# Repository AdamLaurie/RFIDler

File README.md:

# RFIDler

## Firmware

The 'firmware' directory contains code for the dev platform(s).
Currently that is Pic32, but we will add a new section if and when required.

## Hardware

A fully built RFIDler board can be purchased here: [http://rfidiot.org/#Hardware](http://rfidiot.org/#Hardware)

### Pic32

The main microcontroller is a [Microchip PIC32MX795F512L](http://www.microchip.com/wwwproducts/Devices.aspx?dDocName=en545660)

## Software Build environment

The project was developed in Mplab-X IDE V3.20 under Linux, but can also be built under Windows & Mac:

* [Linux] (http://www.microchip.com/mplabx-ide-linux-installer)

* [Windows] (http://www.microchip.com/mplabx-ide-windows-installer)

* [Mac] (http://www.microchip.com/mplabx-ide-osx-installer)

The compiler used was the free version of Microchip's XC32 V1.40:

* [Linux] (http://www.microchip.com/mplabxc32linux)

* [Windows] (http://www.microchip.com/mplabxc32windows)

* [Mac] (http://www.microchip.com/mplabxc32osx)

USB stack and peripheral support is provided by [Microchip Application Library v2013-06-15] (http://www.microchip.com/pagehandler/en-us/devtools/mla/archives.html):

* [Linux](http://ww1.microchip.com/downloads/en/softwarelibrary/microchip-libraries-for-applications-v2013-06-15-linux-installer.run)
  - Install to /opt/microchip/microchip_solutions_v2013-06-15/
  - Note: if the installer fails to start, try adding the run-time option '--mode text'
* [Windows](http://ww1.microchip.com/downloads/en/softwarelibrary/microchip-libraries-for-applications-v2013-06-15-windows-installer.exe)
  - Install to installer default location
* [Mac](http://ww1.microchip.com/downloads/en/softwarelibrary/microchip-libraries-for-applications-v2013-06-15-osx-installer.dmg)
  - Install to installer default location

and [PIC32 Peripheral Library] (http://www.microchip.com/SWLibraryWeb/product.aspx?product=PIC32%20Peripheral%20Library):

* [Linux](http://ww1.microchip.com/downloads/en/DeviceDoc/PIC32%20Legacy%20Peripheral%20Libraries%20Linux.tar)
  - Install to /opt/microchip/xc32/v1.40
* [Windows](http://ww1.microchip.com/downloads/en/DeviceDoc/PIC32%20Legacy%20Peripheral%20Libraries.zip)
  - Install to installer default location
* [Mac](http://ww1.microchip.com/downloads/en/DeviceDoc/PIC32%20Legacy%20Peripheral%20Libraries%20MACOS.zip)
  - Install to installer default location

### Bootloader

When the Bootloader is running the RFIDler appears on the USB as a HID, and waits for new RFIDler firmware to install in Flash memory.
There are several ways of entering the Bootloader, see "Loading new Firmware" section below.

USB HID Bootloader is provided by the [UBW32 project](http://www.schmalzhaus.com/UBW32/FW/HIDBoot.X/HIDBoot.X.zip)

For convenience, a copy of the bootloader hex and an MPLAB hex load project is provided in `firmware/Pic32/HIDBoot_MX795_Hex_Load.X`

The Bootloader client, mphidflash, runs on Linux/Mac/Windows and transmits & verifies the new firmware.

https://github.com/AdamLaurie/mphidflash

#### Notes

mphidflash v1.3 has some known bugs where for some ROM binaries programming fails and a verification error is reported.
	
If you hit this problem check for a newer release of mphidflash. Pre-compiled executables for all platforms are available [here](https://github.com/AdamLaurie/mphidflash)

### Software Build

Install packages as above.

Clone this repo to your local hard disk.

1. Start MPLAB X IDE
2. Choose `File/Open Project/`
3. Browse to RFIDler.X and click 'Open Project'

#### Windows

If you are running Windows, you will need to change the default Linux library to the local Windows version:

UPDATE NEEDED TO THIS SECTION!

(There are bugs in MPLAB X and GNU make such that paths to libraries containing spaces are not always processed correctly, 
and the default install path on Windows contains spaces so making the copy is the simplest solution.)

#### Mac OS X

If you are running Mac OS X, you will need to change the default Linux library to the local Mac version:

UPDATE NEEDED TO THIS SECTION!

### Connections

The device can be powered via the USB port, and, if connected to a PC, will provide a
management CLI/API via USB-Serial CDC at 115200 baud (8 bit, No Parity, 1 Stop Bit, No Handshaking/Flow Control).

The CLI/API is also accessible via 3.3v or 5v UART on pins RG7 (UART3 RX) and RG8 (UART3 TX), also at 115200 baud.

When you connect with USB for the first time, you may need to perform some configuration steps:

#### Linux

Create a rule file for UDEV to allow non-root access to the file, and also disable modem manager access. An appropriate file can be found in the MPLAB project
under the "Linux Support" tab. Copy this file to `/etc/udev/rules.d` and run `sudo udevadm control --reload-rules`

This file can also be found in this repo at: linux-support/71-rfidler-lf-cdc-blacklist.rules

#### Windows

Windows drivers can be found in the 'Windows Driver' tab of the MPLAB project

To connect, any serial terminal emulator should work, but we recommend:

* Linux: minicom (`sudo apt-get install minicom`)
* Windows: [PuTTY](http://www.chiark.greenend.org.uk/~sgtatham/putty/)
* Mac OS X: minicom (install: [brew](https://brew.sh/) minicom) or SerialTools (free from the App Store)

Example linux connection:

	minicom -D /dev/ttyACM1 -b 115200 

Once connected, hit `<ENTER>` to see the HELP screen and switch to CLI mode, or send commands to remain in API mode.

In API mode, all commands are as per CLI mode, and will be ACK'd by a single '.' or NACK'd by '!' if command fails
or '?' if it is not recognised. Other output is command dependant.

## Loading new Firmware

Enter bootloader mode 

* either from the menu (`BL`)
* _or_ by holding down button `BOOTLOADER` while simultaneously 
	* plugging in the USB cable 
	* _or_ pressing the 'RESET' button.

LED6 and LED5 will show stable orange light to confirm bootloader mode has been entered.

	#~/tools/mphidflash-1.6/binaries/mphidflash-1.6-linux-64 -r -w firmware/Pic32/RFIDler.X/dist/debug/production/RFIDler.X.production.hex 
	USB HID device found: 503808 bytes free
	Device family: PIC32

	Erasing...
	Writing hex file 'RFIDler.X.production.hex':......[...removed for brevity...]
	Verifying:.... [...removed for brevity...]
	Resetting device...

You can verify the flashing via `version`

	*RFIDler> version
	0071-beta

### Linux:

`dmesg` should show the following:

	generic-usb 0003:04D8:003C.0003: hiddev0,hidraw1: USB HID v1.11 Device [Microchip Technology Inc. USB HID Bootloader] on usb-0000:00:1d.0-1.1.2.1/input0

To flash the code, `cd` to the top of the repo and run:

		mphidflash -r -w firmware/Pic32/RFIDler.X/dist/default/production/RFIDler.X.production.hex

The device will be programmed and will then reboot. `dmesg` should show:

	usb 2-1.1.2.1: USB disconnect, device number 19
	usb 2-1.1.2.1: new full speed USB device number 20 using ehci_hcd
	cdc_acm 2-1.1.2.1:1.0: This device cannot do calls on its own. It is not a modem.
	cdc_acm 2-1.1.2.1:1.0: ttyACM3: USB ACM device

### Windows

???

### Mac OS X

## Install mphidflash from source
Option 1, v1.6:
```shell
curl https://github.com/AdamLaurie/mphidflash/blob/master/dist/mphidflash-1.6-src.tar.gz > mphidflash1-6.tar.gz
mkdir mphidflash1-6
tar -zxvf mphidflash1-6.tar.gz -C mphidflash1-6
cd mphidflash1-6
mkdir binaries
sudo make install64
```

Option 2, latest:
```shell
git clone https://github.com/AdamLaurie/mphidflash.git
cd mphidflash
sudo make install64
```

## Flash device
```shell
cd #RFIDler repo
mphidflash -r -w firmware/Pic32/RFIDler.X/dist/debug/production/RFIDler.X.production.hex
```

## See Also

(python shell command line interfacee)[python/README.md]

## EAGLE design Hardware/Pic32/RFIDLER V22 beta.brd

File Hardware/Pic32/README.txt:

Rfidler Beta V22 By Zac Franken For Aperture Labs Ltd

These files are licenced under the creative commons licence See the seperate COPYING file

Some of the analog portion of RFIDler comes from a design by edude: http://playground.arduino.cc/Main/DIYRFIDReader#.Uz8tg1cmBaT
which is based on a schematic by Micah Dowty: http://scanlime.org/2008/08/simplest-rfid-reader

Rfidler Hardware Features:

Detection and decoding of ASK, FSK, and PSK RFID Low frequency tags ~125KHz

Emulation of ASK, FSK, and PSK RFID Low frequency tags

Sniffing of ASK, FSK, and PSK RFID Low frequency tags

Adjustment of comparator thresholds via a digital pot via software, a trim pot and a fixed value resistor voltage divider.

SD card interface

Integrated Chip Card interface

Relay driver

USB interface

Serial interface

Wiegand interfaces

User LED

User button

and an as yet untested LC (Inductance and Capacitance) meter circuit (Still in development) for testing the inductance of your own coils.

There is more to come here, but I wanted to get the schematics up as soon as I could.

Zac

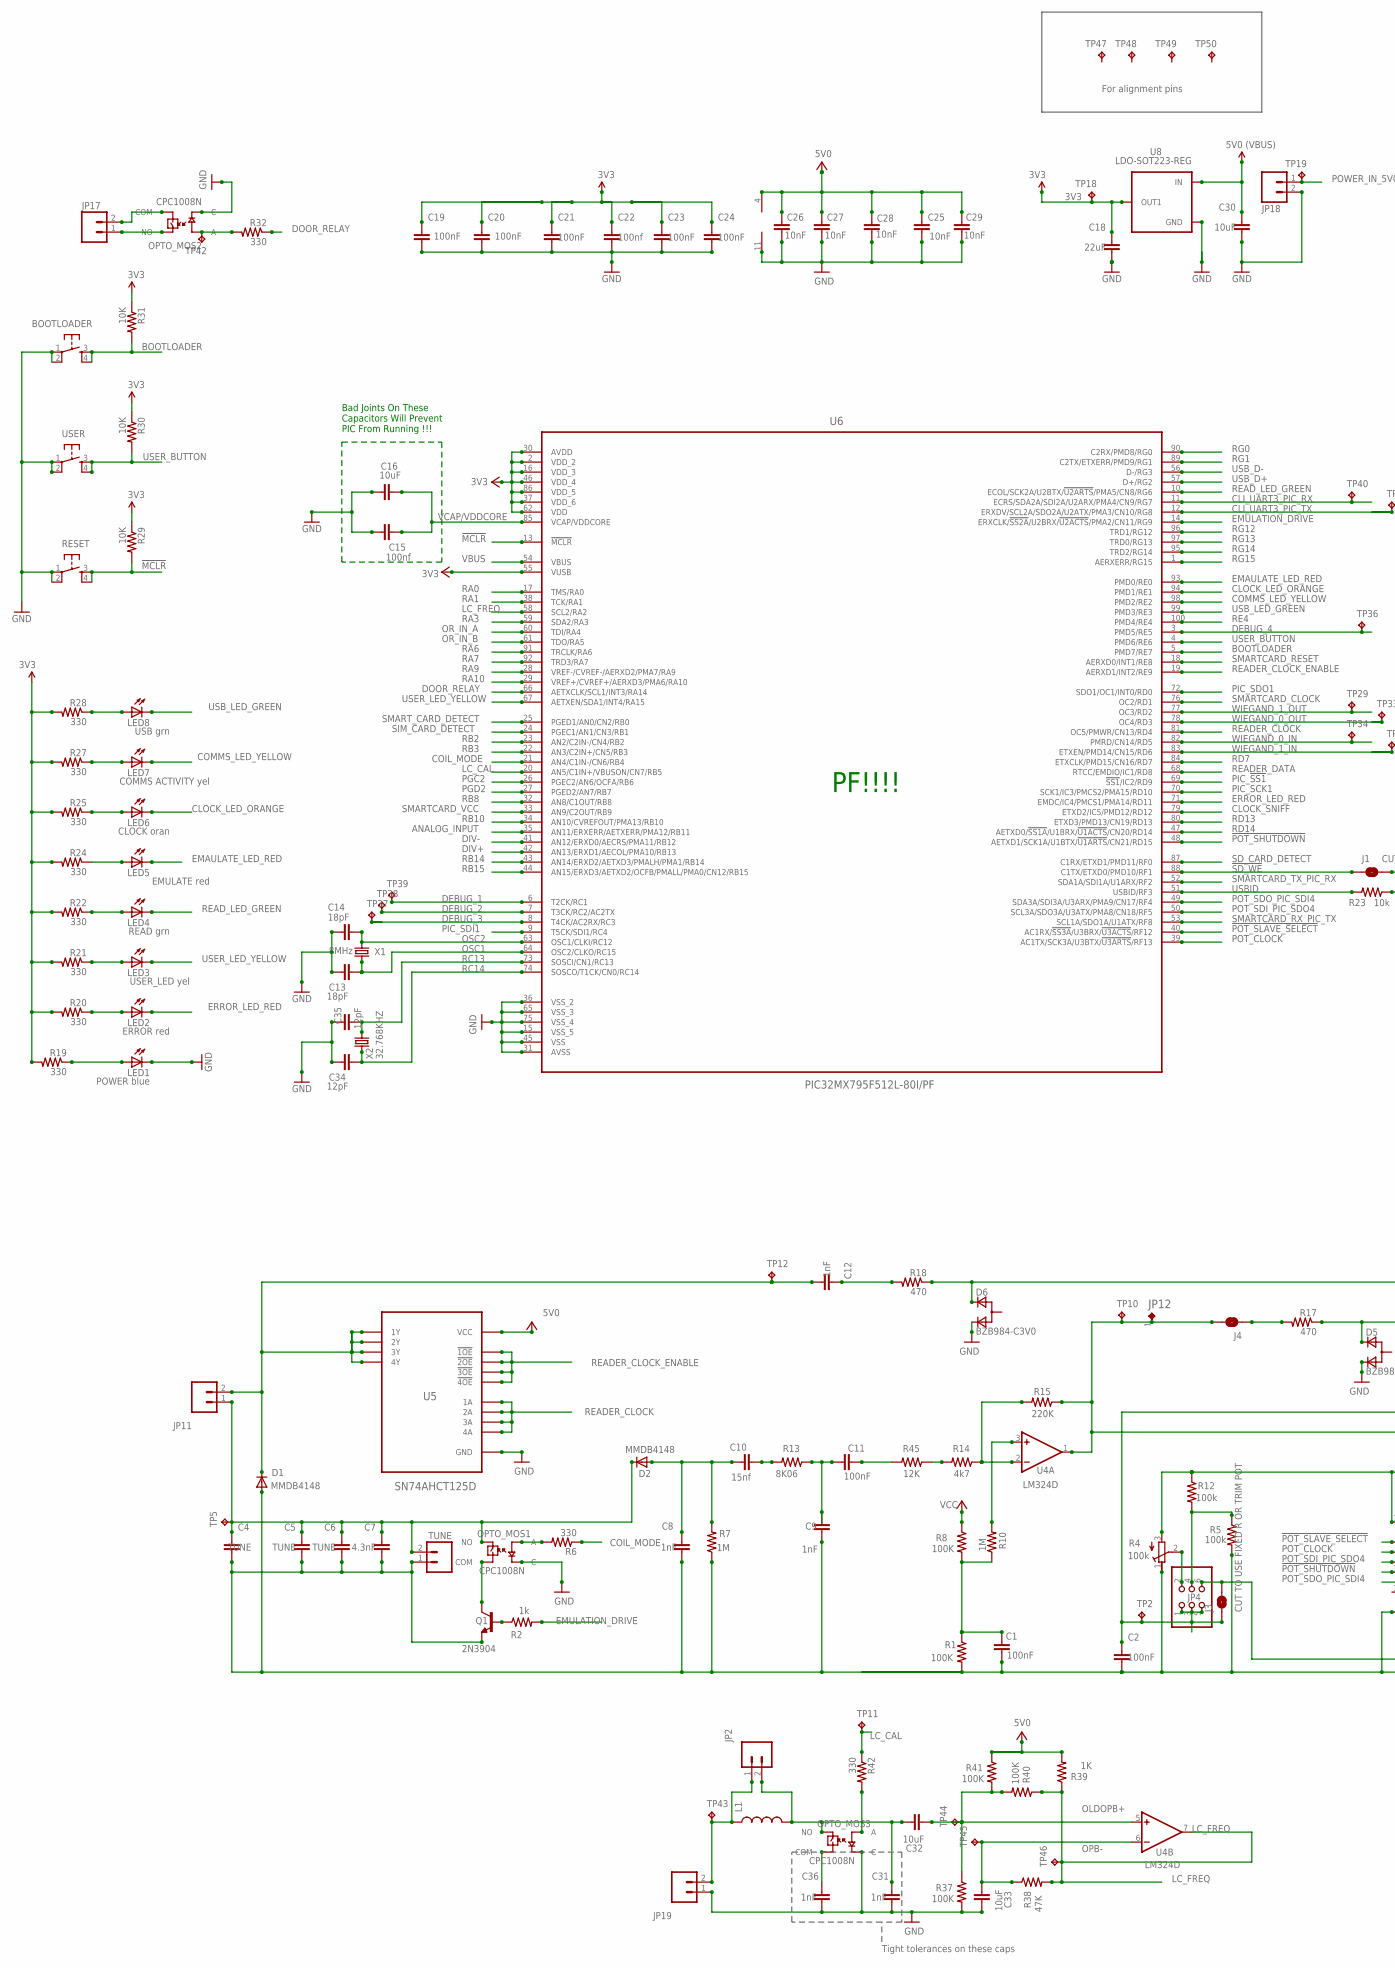
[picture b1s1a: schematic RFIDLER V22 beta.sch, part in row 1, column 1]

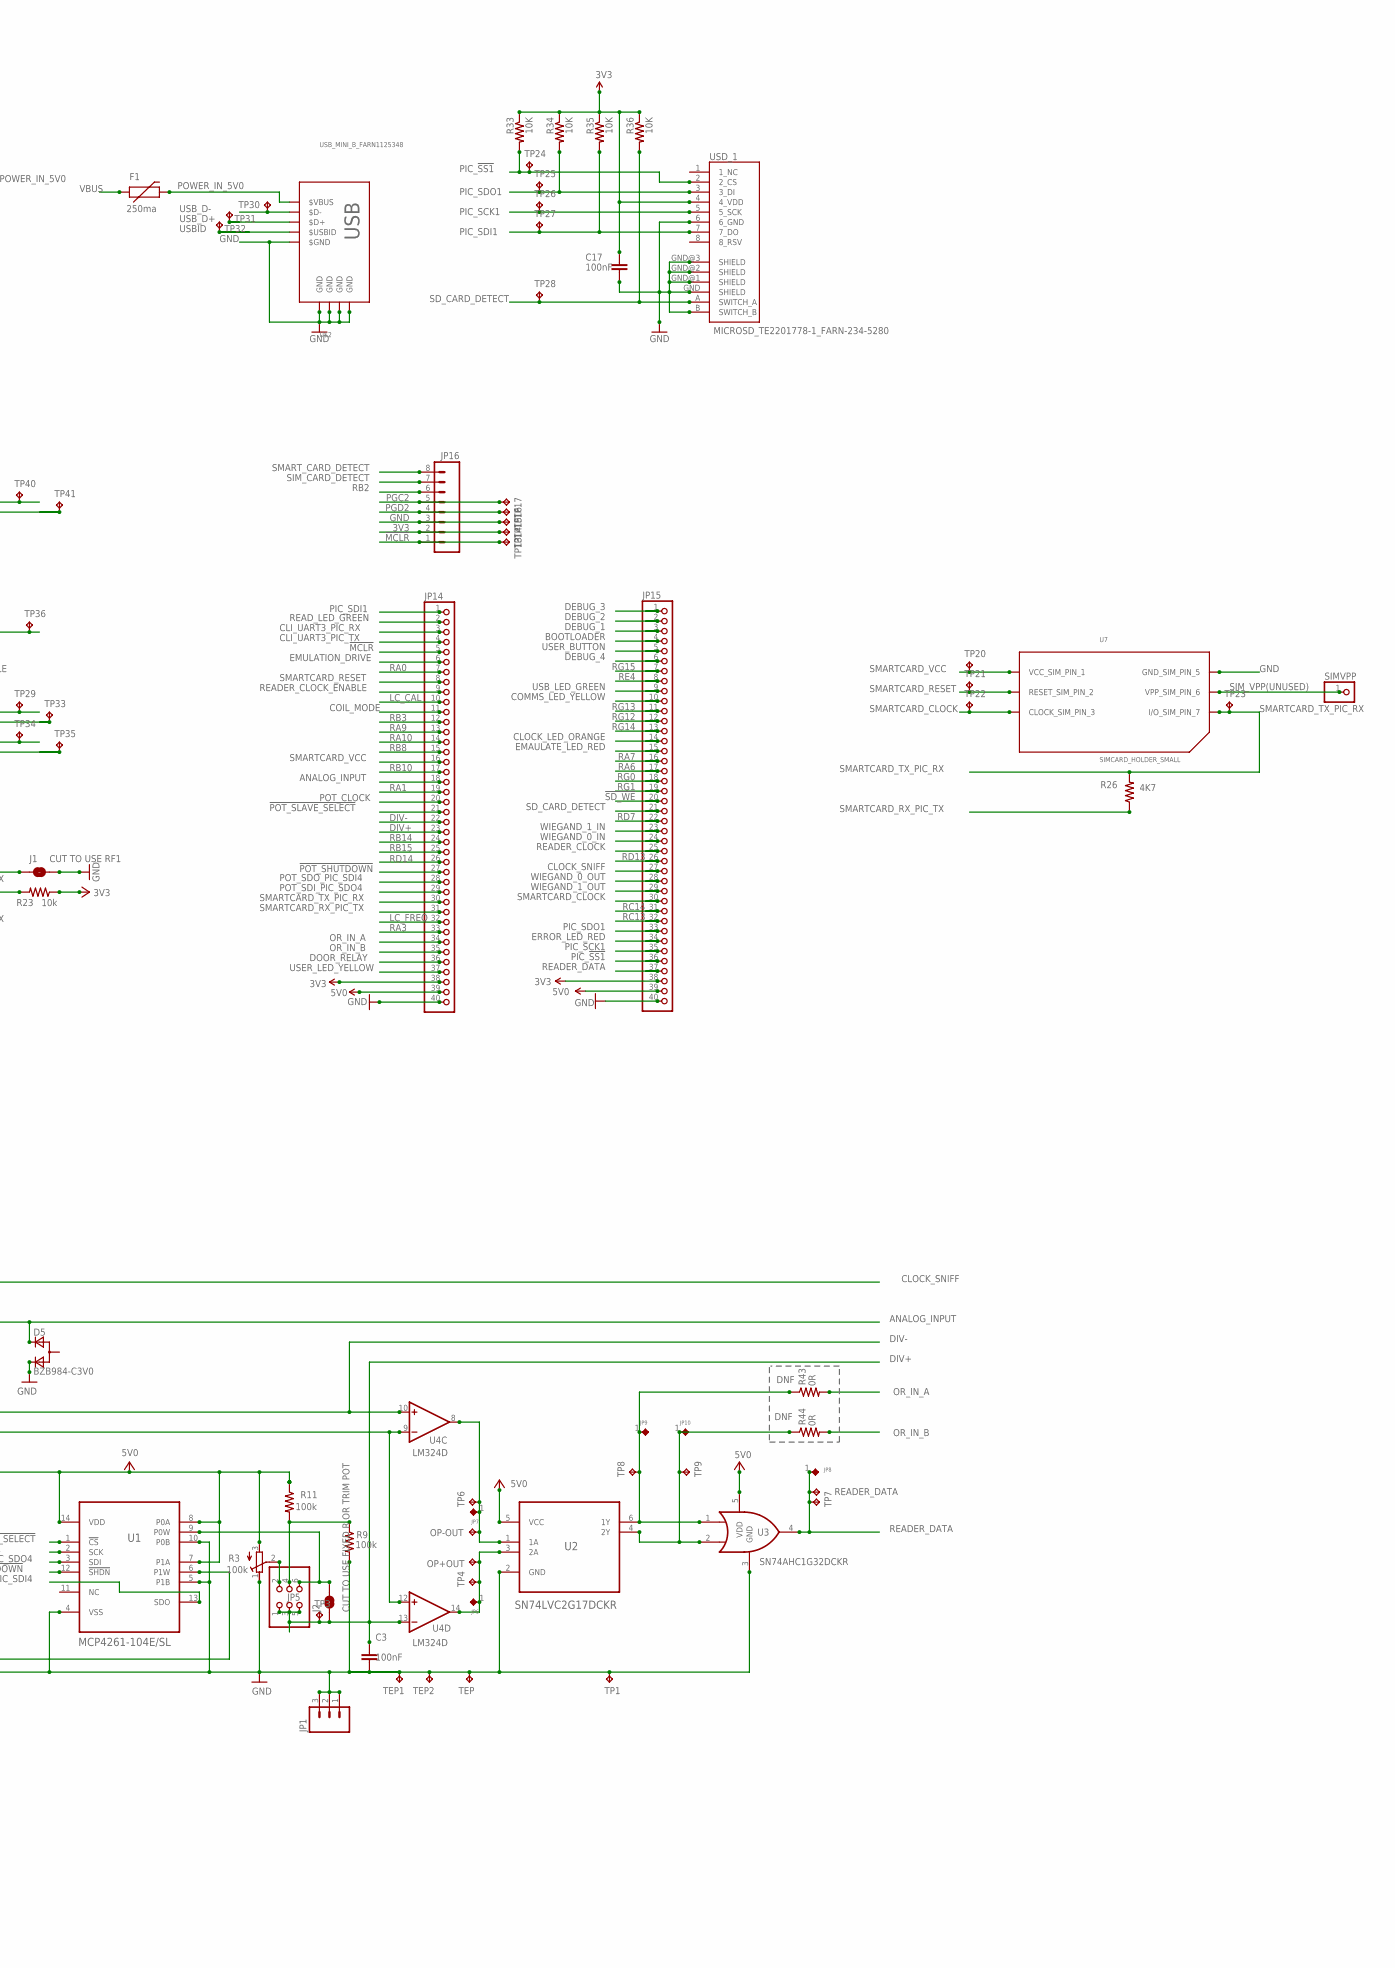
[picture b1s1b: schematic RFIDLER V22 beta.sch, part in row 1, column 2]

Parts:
BOOTLOADER: TAC_SWITCHSMD; TACTILE_SWITCH_SMD; TOLERANCE ?; FARNELL 9471880
C1: 100nF; 0603-CAP; TOLERANCE ?; PARTNO currently rs 264-4646; FARNELL 2332586
C2: 100nF; C0603; TOLERANCE ?; PARTNO currently rs 264-4646; FARNELL 2332586
C3: 100nF; C0603; TOLERANCE ?; PARTNO ?; FARNELL 2332586
C4, C5, C6: TUNE; C0603; TOLERANCE ?; PARTNO ?; FARNELL DNF
C7: 4.3nF; C0603; TOLERANCE 1%; PARTNO ?; FARNELL 1865494
C8, C9, C12: 1nF; C0603; TOLERANCE ?; PARTNO ?; FARNELL 1414606
C10: 15nf; C0603; TOLERANCE ?; PARTNO ?; FARNELL 2070401
C11: 100nF; C0603; TOLERANCE ?; PARTNO currently rs2644646; FARNELL 2332586
C13, C14: 18pF; C0603; TOLERANCE ?; FARNELL 1612182
C15: 100nf; C0603; TOLERANCE Cuurently rs 264 4646; FARNELL 2332586
C16, C30: 10uF; C0805; TOLERANCE ?; FARNELL 1867958
C17: 100nF; C0603; TOLERANCE Crrently rs 264 4646; FARNELL DNF
C18: 22uF; C0805; TOLERANCE ?; FARNELL 1867956
C19, C20, C21, C23, C24: 100nF; C0603; TOLERANCE Crrently rs 264 4646; FARNELL 2332586
C22: 100nf; C0603; TOLERANCE Crrently rs 264 4646; FARNELL 2332586
C25, C26, C27, C28, C29: 10nF; C0603; TOLERANCE ?; PARTNO ?; FARNELL 1301715
C31, C36: 1nF; C0603; TOLERANCE ?; PARTNO ?; FARNELL DNF
C32, C33: 10uF; C0805; TOLERANCE ?; FARNELL DNF
C34, C35: 12pF; C0603; TOLERANCE ?; FARNELL DNF
D1, D2: MMDB4148; SOT23-3; TOLERANCE ?; PARTNO ?; FARNELL 2069338
D5, D6: BZB984-C3V0; SOT663; FARNELL 8735310
F1: 250ma; PTC-1206; FARNELL 1596990
J1: CUT TO USE RF1; SJ_2S-TRACE
J2, J3: CUT TO USE FIXED R OR TRIM POT; SJ_2S-TRACE
J4: SOLDERJUMPERTRACE; SJ_2S-TRACE
JP1: M03LOCK_LONGPADS; 1X03_LOCK_LONGPADS; FARNELL DNF
JP2, JP18, JP19: M02LOCK_LONGPADS; 1X02_LOCK_LONGPADS; TOLERANCE ?; PARTNO ?; FARNELL DNF
JP4, JP5: PINHD-2X3; 2X03; TOLERANCE ?; PARTNO ?; FARNELL DNF
JP6, JP7, JP8, JP9, JP10, JP12: PINHD-1X1; 1X01; TOLERANCE ?; FARNELL DNF
JP11: M02LOCK_LONGPADS; 1X02_LOCK_LONGPADS; TOLERANCE ?; PARTNO ?; FARNELL 1550562 standard 2 PIN HEADER
JP14, JP15: PINHD-1X40; 1X40; FARNELL DNF
JP16: M08; 1X08; TOLERANCE ?; FARNELL DNF
JP17: M02LOCK_LONGPADS; 1X02_LOCK_LONGPADS; FARNELL DNF
L1: INDUCTOR0603; 0603; FARNELL DNF
LED1: POWER blue; LED-0603; TOLERANCE ?; FARNELL 2217972
LED2: ERROR red; LED-0603; TOLERANCE ?; FARNELL 2099221
LED3: USER_LED yel; LED-0603; TOLERANCE ?; FARNELL 2146436
LED4: READ grn; LED-0603; TOLERANCE ?; FARNELL 2146434
LED5: EMULATE red; LED-0603; TOLERANCE ?; FARNELL 2099221
LED6: CLOCK oran; LED-0603; TOLERANCE ?; FARNELL 2146433
LED7: COMMS ACTIVITY yel; LED-0603; TOLERANCE ?; FARNELL 2146436
LED8: USB grn; LED-0603; TOLERANCE ?; FARNELL 2146434
OP+OUT: TPPAD1-13; P1-13; TOLERANCE ?; PARTNO ?; FARNELL ?
OP-OUT: TPPAD1-13; P1-13; TOLERANCE ?; PARTNO ?; FARNELL ?
OPTO_MOS1: CPC1008N; FARNELL 1653755
OPTO_MOS2, OPTO_MOS3: CPC1008N; FARNELL DNF
Q1: 2N3904; SOT323; TOLERANCE ?; PARTNO ?; FARNELL 1459102
R1, R8: 100K; R0603; TOLERANCE ?; PARTNO ?; FARNELL 9330402
R2: 1k; R0603; TOLERANCE ?; PARTNO ?; FARNELL 9238484
R3, R4: 100k; RTRIMT93XA; TOLERANCE ?; PARTNO ?; FARNELL DNF
R5, R9, R11, R12: 100k; R0603; TOLERANCE ?; PARTNO ?; FARNELL 9330402
R6, R19, R20, R21, R22, R24, R25, R27, R28: 330; R0603; TOLERANCE ?; FARNELL 9332014
R7, R10: 1M; R0603; TOLERANCE ?; PARTNO ?; FARNELL 1469746
R13: 8K06; R0603; TOLERANCE ?; PARTNO ?; FARNELL 1170881
R14: 4k7; R0603; TOLERANCE ?; PARTNO ?; FARNELL 2078913
R15: 220K; R0603; TOLERANCE ?; PARTNO ?; FARNELL 2073431
R17, R18: 470; R0603; TOLERANCE ?; FARNELL 2333530
R23: 10k; R0603; TOLERANCE ?; PARTNO ?; FARNELL 9330399
R26: 4K7; R0603; TOLERANCE ?; PARTNO ?; FARNELL DNF
R29, R30, R31: 10K; R0603; TOLERANCE ?; FARNELL 9330399
R32, R42: 330; R0603; TOLERANCE ?; FARNELL DNF
R33, R34, R35, R36: 10K; R0603; TOLERANCE ?; FARNELL DNF
R37, R40, R41: 100K; R0603; TOLERANCE ?; PARTNO ?; FARNELL DNF
R38: 47K; R0603; TOLERANCE ?; PARTNO ?; FARNELL DNF
R39: 1K; R0603; TOLERANCE ?; PARTNO ?; FARNELL DNF
R43, R44: 0R; R0603; TOLERANCE ?; PARTNO ?; FARNELL DNF
R45: 12K; R0603; TOLERANCE ?; PARTNO ?; FARNELL 1652834
READER_DATA: TPPAD1-13; P1-13; TOLERANCE ?; PARTNO ?; FARNELL DNF
RESET: TAC_SWITCHSMD; TACTILE_SWITCH_SMD; TOLERANCE ?; FARNELL 9471880
SIMVPP: PINHD-1X1; 1X01; FARNELL DNF
TEP, TEP1, TEP2: TPPAD1-13; P1-13; TOLERANCE ?; PARTNO ?; FARNELL DNF
TP1, TP9, TP18: DOWNS_ORIN1; TP20R
TP2: DIV-; TP20R
TP3: DIV+; TP20R
TP4: OP-OUT; TP20R
TP5: COIL_B; TP20R
TP6: OP+OUT; TP20R
TP7: READER_DATA; TP20R
TP8: UPS_ORIN1; TP20R
TP10: RAW_READER_OUT; TP20R
TP11: LC_CAL; TP20R
TP12: COIL_A; TP20R
TP13: !MCLR; TP20R
TP14: 3V3; TP20R
TP15: GND; TP20R
TP16: PGD2; TP20R
TP17: PGC2; TP20R
TP19: POWER_IN_5V0; TP20R
TP20: SMARTCARD_VCC; TP20R
TP21: SMARTCARD_RESET; TP20R
TP22: SMARTCARD_CLOCK; TP20R
TP23: SMARTCARD_TX_PIC_RX; TP20R
TP24: PIC_!SS1; TP20R
TP25: PIC_SDO1; TP20R
TP26: PIC_SCK1; TP20R
TP27: PIC_SDI1; TP20R
TP28: SD_CARD_DETECT; TP20R
TP29: WIEGAND_1_OUT; TP20R
TP30: USB_D-; TP20R
TP31: USB_D+; TP20R
TP32: USBID; TP20R
TP33: WIE0OUT; TP20R
TP34: WIE0IN; TP20R
TP35: WIE1IN; TP20R
TP36: DEBUG_4; TP20R
TP37: DEBUG_3; TP20R
TP38: DEBUG_2; TP20R
TP39: DEBUG_1; TP20R
TP40: CLI_UART3_PIC_RX; TP20R
TP41: CLI_UART3_PIC_TX; TP20R
TP42: RELAY; TP20R
TP43: LC_COIL; TP20R
TP44: LC+; TP20R
TP45: LC-; TP20R
TP46: LCOUT; TP20R
TP47: PEG4; TP20R
TP48: PEG1; TP20R
TP49: PEG3; TP20R
TP50: PEG2; TP20R
TUNE: M02LOCK_LONGPADS; 1X02_LOCK_LONGPADS; TOLERANCE ?; PARTNO ?; FARNELL DNF
U1: MCP4261-104E/SL; SOIC127P600X175-14N; TOLERANCE ?; PARTNO ?; FARNELL 1840694
U2: SN74LVC2G17DCKR; SOT65P210X110-6N; TOLERANCE ?; PARTNO ?; FARNELL 1287569
U3: SN74AHC1G32DCKR; SC70-5L; TOLERANCE ?; PARTNO ?; FARNELL 1287449
U4: LM324D; SO14; TOLERANCE ?; PARTNO ?; FARNELL 8389233
U5: SN74AHCT125D; SOIC127P600X175-14N; FARNELL 1287453
U6: PIC32MX795F512L-80I/PF; QFP50P1600X1600X120-100N; TOLERANCE ?; FARNELL 1778491
U7: SIMCARD_HOLDER_SMALL; SIM_CARD_CONN; FARNELL DNF
U8: LDO-SOT223-REG; SOT223; FARNELL 9778195
U$2: USB_MINI_B_FARN1125348; FARNELL 1125348
USD_1: MICROSD_TE2201778-1_FARN-234-5280; FARNELL DNF
USER: TAC_SWITCHSMD; TACTILE_SWITCH_SMD; TOLERANCE ?; FARNELL 9471880
X1: 8MHz; HC49UP; TOLERANCE ?; FARNELL 1842346
X2: 32.768KHZ; TC38H; FARNELL DNF

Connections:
3V3: C17.1, C18.1, C19.1, C20.1, C21.1, C22.1, C23.1, C24.1, JP14.38, JP15.38, JP16.2, R19.2, R20.2, R21.2, R22.2, R23.1, R24.2, R25.2, R27.2, R28.2, R29.1, R30.1, R31.1, R33.1, R34.1, R35.1, R36.1, TP14.TP, TP18.TP, U6.2 (VDD_2), U6.16 (VDD_3), U6.30 (AVDD), U6.37 (VDD_6), U6.46 (VDD_4), U6.55 (VUSB), U6.62 (VDD), U6.86 (VDD_5), U8.P$2@2 (OUT1), USD_1.4 (4_VDD)
!MCLR: JP14.5, JP16.1, R29.2, RESET.3, RESET.4, TP13.TP, U6.13 (!MCLR)
!POT_SHUTDOWN: JP14.27, U1.12 (!SHDN), U6.48 (AETXD1/SCK1A/U1BTX/!U1ARTS!/CN21/RD15)
!POT_SLAVE_SELECT: JP14.21, U1.1 (!CS), U6.40 (AC1RX/!SS3A!/U3BRX/!U3ACTS!/RF12)
!SD_WE: J1.1, JP15.20, U6.88 (C1TX/ETXD0/PMD10/RF1)
ANALOG_INPUT: D5.P$1 (C1), JP14.18, R17.1, U6.35 (AN11/ERXERR/AETXERR/PMA12/RB11)
BOOTLOADER: BOOTLOADER.3, BOOTLOADER.4, JP15.4, R31.2, U6.5 (PMD7/RE7)
CLI_UART3_PIC_RX: JP14.3, TP40.TP, U6.11 (ECRS/SDA2A/SDI2A/U2ARX/PMA4/CN9/RG7)
CLI_UART3_PIC_TX: JP14.4, TP41.TP, U6.12 (ERXDV/SCL2A/SDO2A/U2ATX/PMA3/CN10/RG8)
CLOCK: C12.2, D1.3 (C), JP11.2, TP12.TP, U5.3 (1Y), U5.6 (2Y), U5.8 (3Y), U5.11 (4Y)
CLOCK_LED_ORANGE: JP15.14, LED6.C, U6.94 (PMD1/RE1)
CLOCK_SNIFF: D6.P$1 (C1), JP15.27, R18.1, U6.79 (ETXD2/IC5/PMD12/RD12)
COIL: C4.1, C5.1, C6.1, C7.1, D2.3 (C), JP11.1, OPTO_MOS1.NO, TP5.TP, TUNE.2
COIL_MODE: JP14.11, R6.1, U6.21 (AN4/C1IN-/CN6/RB4)
COMMS_LED_YELLOW: JP15.10, LED7.C, U6.98 (PMD2/RE2)
DEBUG_1: JP15.3, TP39.TP, U6.6 (T2CK/RC1)
DEBUG_2: JP15.2, TP38.TP, U6.7 (T3CK/RC2/AC2TX)
DEBUG_3: JP15.1, TP37.TP, U6.8 (T4CK/AC2RX/RC3)
DEBUG_4: JP15.6, TP36.TP, U6.3 (PMD5/RE5)
DIV+: C3.1, J2.1, JP5.1, JP5.3, JP5.5, JP14.23, TP3.TP, U4.13 (-IN), U6.42 (AN13/ERXD1/AECOL/PMA10/RB13)
DIV-: C2.1, J3.1, JP4.1, JP4.3, JP4.5, JP14.22, TP2.TP, U4.10 (+IN), U6.41 (AN12/ERXD0/AECRS/PMA11/RB12)
DOOR_RELAY: JP14.36, R32.1, U6.66 (AETXCLK/SCL1/INT3/RA14)
DOWNS_ORIN1: JP10.1, R44.1, TP9.TP, U2.4 (2Y), U3.2 (B)
EMAULATE_LED_RED: JP15.15, LED5.C, U6.93 (PMD0/RE0)
EMULATION_DRIVE: JP14.6, R2.2, U6.14 (ERXCLK/!SS2A!/U2BRX/!U2ACTS!/PMA2/CN11/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)
ERROR_LED_RED: JP15.34, LED2.C, U6.71 (EMDC/IC4/PMCS1/PMA14/RD11)
GND: BOOTLOADER.1, BOOTLOADER.2, C1.2, C2.2, C3.2, C4.2, C5.2, C6.2, C7.2, C8.2, C9.1, C13.1, C14.1, C15.2, C16.2, C17.2, C18.2, C19.2, C20.2, C21.2, C22.2, C23.2, C24.2, C25.1, C26.2, C27.2, C28.2, C29.2, C30.2, C31.2, C33.1, C34.1, C35.1, C36.2, D1.1 (A), D5.P$2 (C2), D6.P$2 (C2), J1.2, JP1.1, JP1.2, JP1.3, JP14.40, JP15.40, JP16.3, JP18.2, JP19.1, LED1.C, OPTO_MOS1.C, OPTO_MOS2.C, OPTO_MOS3.C, Q1.3 (E), R1.2, R3.1 (A), R4.1 (A), R5.2, R7.1, R9.2, R37.2, RESET.1, RESET.2, TEP.TP, TEP1.TP, TEP2.TP, TP1.TP, TP15.TP, TUNE.1, U1.4 (VSS), U1.5 (P1B), U1.10 (P0B), U2.2 (GND), U3.3 (GND), U4.11 (V-), U5.7 (GND), U6.15 (VSS_5), U6.31 (AVSS), U6.36 (VSS_2), U6.45 (VSS), U6.65 (VSS_3), U6.75 (VSS_4), U7.CARD_GND_PIN5 (GND_SIM_PIN_5), U8.P$1 (GND), U$2.GND ($GND), U$2.GND@1 (GND), U$2.GND@2 (GND), U$2.GND@3 (GND), U$2.GND@4 (GND), USD_1.6 (6_GND), USD_1.B (SWITCH_B), USD_1.GND (SHIELD), USD_1.GND@1 (SHIELD), USD_1.GND@2 (SHIELD), USD_1.GND@3 (SHIELD), USER.1, USER.2
LC_CAL: JP14.10, R42.1, TP11.TP, U6.20 (AN5/C1IN+/VBUSON/CN7/RB5)
LC_COIL: C31.1, C32.1, JP2.2, L1.2, OPTO_MOS3.NO
LC_FREQ: JP14.32, R38.2, R39.1, R40.1, TP46.TP, U4.7 (OUT), U6.58 (SCL2/RA2)
unnamed: JP4.2, R4.2 (S)
unnamed: OPTO_MOS3.A, R42.2
unnamed: C36.1, OPTO_MOS3.COM
unnamed: C8.1, C10.1, D2.1 (A), R7.2
unnamed: C10.2, R13.2
unnamed: C9.2, C11.2, R13.1
unnamed: C11.1, R45.2
unnamed: R14.1, R15.2, U4.2 (-IN)
unnamed: Q1.1 (B), R2.1
unnamed: JP2.1, JP19.2, L1.1, TP43.TP
unnamed: R10.2, U4.3 (+IN)
unnamed: J3.2, JP4.6, U1.6 (P1W)
unnamed: LED4.A, R22.1
unnamed: JP5.2, R3.2 (S)
unnamed: LED3.A, R21.1
unnamed: J2.2, JP5.6, U1.9 (P0W)
unnamed: OPTO_MOS1.COM, Q1.2 (C)
unnamed: JP4.4, R5.1, R12.2
unnamed: OPTO_MOS1.A, R6.2
unnamed: JP5.4, R9.1, R11.2
unnamed: C12.1, R18.2
unnamed: LED1.A, R19.1
unnamed: LED2.A, R20.1
unnamed: OPTO_MOS2.A, R32.2, TP42.TP
unnamed: JP17.1, OPTO_MOS2.NO
unnamed: JP17.2, OPTO_MOS2.COM
unnamed: J4.1, R17.2
unnamed: R14.2, R45.1
unnamed: LED8.A, R28.1
unnamed: LED7.A, R27.1
unnamed: LED5.A, R24.1
unnamed: LED6.A, R25.1
OLDOPB+: C32.2, R37.1, R40.2, R41.2, TP44.TP, U4.5 (+IN)
OP+OUT: JP7.1, OP-OUT.TP, TP6.TP, U2.1 (1A), U4.8 (OUT)
OP-OUT: JP6.1, OP+OUT.TP, TP4.TP, U2.3 (2A), U4.14 (OUT)
OPB-: C33.2, R38.1, TP45.TP, U4.6 (-IN)
OR_IN_A: JP14.34, R43.2, U6.60 (TDI/RA4)
OR_IN_B: JP14.35, R44.2, U6.61 (TDO/RA5)
OSC1: C13.2, U6.64 (OSC2/CLKO/RC15), X1.1
OSC2: C14.2, U6.63 (OSC1/CLKI/RC12), X1.2
PGC2: JP16.5, TP17.TP, U6.26 (PGEC2/AN6/OCFA/RB6)
PGD2: JP16.4, TP16.TP, U6.27 (PGED2/AN7/RB7)
PIC_!SS1: JP15.36, R33.2, TP24.TP, U6.69 (!SS1!/IC2/RD9), USD_1.2 (2_CS)
PIC_SCK1: JP15.35, TP26.TP, U6.70 (SCK1/IC3/PMCS2/PMA15/RD10), USD_1.5 (5_SCK)
PIC_SDI1: JP14.1, R35.2, TP27.TP, U6.9 (T5CK/SDI1/RC4), USD_1.7 (7_DO)
PIC_SDO1: JP15.33, R34.2, TP25.TP, U6.72 (SDO1/OC1/INT0/RD0), USD_1.3 (3_DI)
POT_CLOCK: JP14.20, U1.2 (SCK), U6.39 (AC1TX/SCK3A/U3BTX/!U3ARTS!/RF13)
POT_SDI_PIC_SDO4: JP14.29, U1.3 (SDI), U6.50 (SCL3A/SDO3A/U3ATX/PMA8/CN18/RF5)
POT_SDO_PIC_SDI4: JP14.28, U1.13 (SDO), U6.49 (SDA3A/SDI3A/U3ARX/PMA9/CN17/RF4)
POWER_IN_5V0: F1.2, JP18.1, TP19.TP, U$2.VBUS ($VBUS)
RA0: JP14.7, U6.17 (TMS/RA0)
RA1: JP14.19, U6.38 (TCK/RA1)
RA3: JP14.33, U6.59 (SDA2/RA3)
RA6: JP15.17, U6.91 (TRCLK/RA6)
RA7: JP15.16, U6.92 (TRD3/RA7)
RA9: JP14.13, U6.28 (VREF-/CVREF-/AERXD2/PMA7/RA9)
RA10: JP14.14, U6.29 (VREF+/CVREF+/AERXD3/PMA6/RA10)
RAW_READER_OUT: J4.2, JP12.1, R15.1, TP10.TP, U4.1 (OUT), U4.9 (-IN), U4.12 (+IN)
RB2: JP16.6, U6.23 (AN2/C2IN-/CN4/RB2)
RB3: JP14.12, U6.22 (AN3/C2IN+/CN5/RB3)
RB8: JP14.15, U6.32 (AN8/C1OUT/RB8)
RB10: JP14.17, U6.34 (AN10/CVREFOUT/PMA13/RB10)
RB14: JP14.24, U6.43 (AN14/ERXD2/AETXD3/PMALH/PMA1/RB14)
RB15: JP14.25, U6.44 (AN15/ERXD3/AETXD2/OCFB/PMALL/PMA0/CN12/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)
RC13: C35.2, JP15.32, U6.73 (SOSCI/CN1/RC13), X2.2
RC14: C34.2, JP15.31, U6.74 (SOSCO/T1CK/CN0/RC14), X2.1
RD7: JP15.22, U6.84 (ETXCLK/PMD15/CN16/RD7)
RD13: JP15.26, U6.80 (ETXD3/PMD13/CN19/RD13)
RD14: JP14.26, U6.47 (AETXD0/!SS1A!/U1BRX/!U1ACTS!/CN20/RD14)
RE4: JP15.8, U6.100 (PMD4/RE4)
READER_CLOCK: JP15.25, U5.2 (1A), U5.5 (2A), U5.9 (3A), U5.12 (4A), U6.81 (OC5/PMWR/CN13/RD4)
READER_CLOCK_ENABLE: JP14.9, U5.1 (!1OE), U5.4 (!2OE), U5.10 (!3OE), U5.13 (!4OE), U6.19 (AERXD1/INT2/RE9)
READER_DATA: JP8.1, JP15.37, READER_DATA.TP, TP7.TP, U3.4 (Y), U6.68 (RTCC/EMDIO/IC1/RD8)
READ_LED_GREEN: JP14.2, LED4.C, U6.10 (ECOL/SCK2A/U2BTX/!U2ARTS!/PMA5/CN8/RG6)
RG0: JP15.18, U6.90 (C2RX/PMD8/RG0)
RG1: JP15.19, U6.89 (C2TX/ETXERR/PMD9/RG1)
RG12: JP15.12, U6.96 (TRD1/RG12)
RG13: JP15.11, U6.97 (TRD0/RG13)
RG14: JP15.13, U6.95 (TRD2/RG14)
RG15: JP15.7, U6.1 (AERXERR/RG15)
SD_CARD_DETECT: JP15.21, R36.2, TP28.TP, U6.87 (C1RX/ETXD1/PMD11/RF0), USD_1.A (SWITCH_A)
SIM_CARD_DETECT: JP16.7, U6.24 (PGEC1/AN1/CN3/RB1)
SIM_VPP(UNUSED): SIMVPP.1, U7.CARD_VPP_PIN6 (VPP_SIM_PIN_6)
SMARTCARD_CLOCK: JP15.30, TP22.TP, U6.76 (OC2/RD1), U7.CARD_CLK_PIN3 (CLOCK_SIM_PIN_3)
SMARTCARD_RESET: JP14.8, TP21.TP, U6.18 (AERXD0/INT1/RE8), U7.CARD_RESET_PIN2 (RESET_SIM_PIN_2)
SMARTCARD_RX_PIC_TX: JP14.31, R26.1, U6.53 (SCL1A/SDO1A/U1ATX/RF8)
SMARTCARD_TX_PIC_RX: JP14.30, R26.2, TP23.TP, U6.52 (SDA1A/SDI1A/U1ARX/RF2), U7.CARD_IO_PIN7 (I/O_SIM_PIN_7)
SMARTCARD_VCC: JP14.16, TP20.TP, U6.33 (AN9/C2OUT/RB9), U7.CARD_VCC_PIN1 (VCC_SIM_PIN_1)
SMART_CARD_DETECT: JP16.8, U6.25 (PGED1/AN0/CN2/RB0)
UPS_ORIN1: JP9.1, R43.1, TP8.TP, U2.6 (1Y), U3.1 (A)
USBID: R23.2, TP32.TP, U6.51 (USBID/RF3), U$2.ID ($USBID)
USB_D+: TP31.TP, U6.57 (D+/RG2), U$2.D+ ($D+)
USB_D-: TP30.TP, U6.56 (D-/RG3), U$2.D- ($D-)
USB_LED_GREEN: JP15.9, LED8.C, U6.99 (PMD3/RE3)
USER_BUTTON: JP15.5, R30.2, U6.4 (PMD6/RE6), USER.3, USER.4
USER_LED_YELLOW: JP14.37, LED3.C, U6.67 (AETXEN/SDA1/INT4/RA15)
VBUS: C25.2, C26.1, C27.1, C28.1, C29.1, C30.1, F1.1, JP14.39, JP15.39, R3.3 (E), R4.3 (E), R8.1, R11.1, R12.1, R39.2, R41.1, U1.7 (P1A), U1.8 (P0A), U1.14 (VDD), U2.5 (VCC), U3.5 (VDD), U4.4 (V+), U5.14 (VCC), U6.54 (VBUS), U8.P$3 (IN)
VCAP/VDDCORE: C15.1, C16.1, U6.85 (VCAP/VDDCORE)
VDIVBIAS: C1.1, R1.1, R8.2, R10.1
WIEGAND_0_IN: JP15.24, TP34.TP, U6.82 (PMRD/CN14/RD5)
WIEGAND_0_OUT: JP15.28, TP33.TP, U6.78 (OC4/RD3)
WIEGAND_1_IN: JP15.23, TP35.TP, U6.83 (ETXEN/PMD14/CN15/RD6)
WIEGAND_1_OUT: JP15.29, TP29.TP, U6.77 (OC3/RD2)

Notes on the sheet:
PF!!!!
Bad Joints On These Capacitors Will Prevent PIC From Running !!!
Tight tolerances on these caps
DNF
For alignment pins

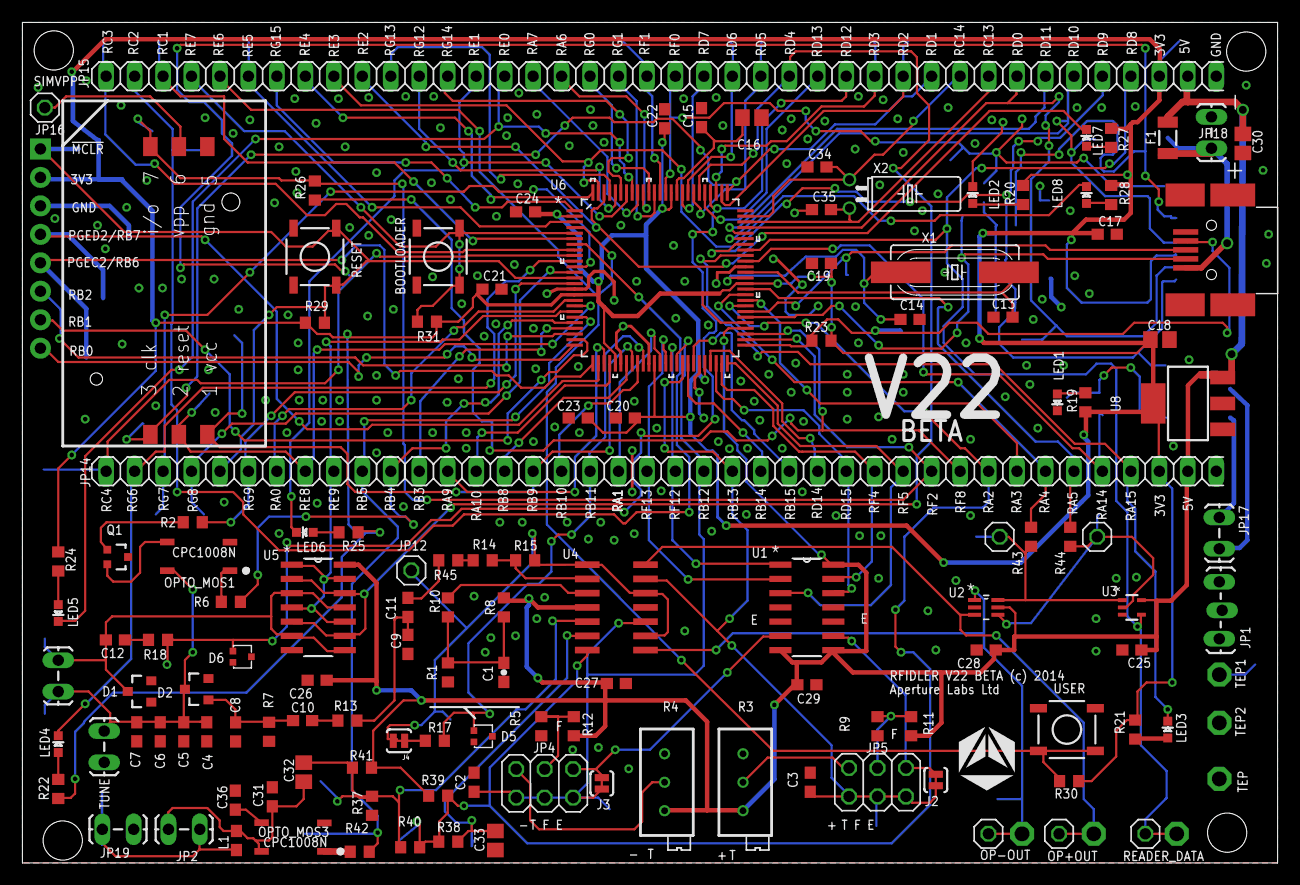
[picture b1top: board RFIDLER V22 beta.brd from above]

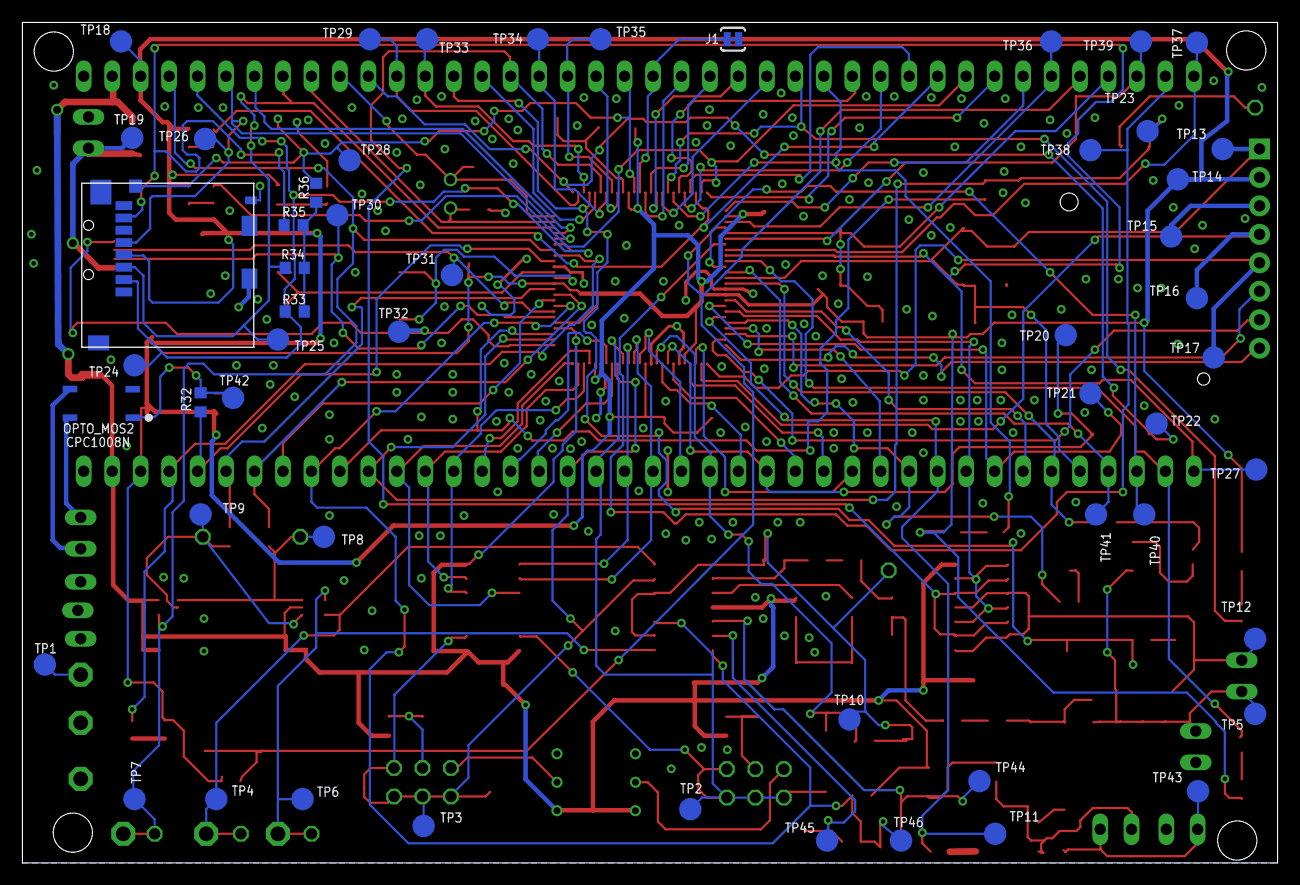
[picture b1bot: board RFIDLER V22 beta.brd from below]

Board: 2 copper layers, 112.0 x 75.0 mm, 193 parts (58 on the bottom side), 133 nets.

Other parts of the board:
U$1: AP_LOGO_5MM_SILK

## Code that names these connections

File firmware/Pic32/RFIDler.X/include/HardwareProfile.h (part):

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#define mLED_Only_Comms_On()    {mLED_USB_Off();mLED_Comms_On();}

/** SWITCH *********************************************************/
#define swBootloader        PORTEbits.RE7
#define swUser              PORTEbits.RE6

/** I/O pin definitions ********************************************/
#define INPUT_PIN                   1
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#define CLOCK_OFF                   HIGH

// output coil control - select between reader/emulator circuits
#define COIL_MODE                  LATBbits.LATB4
#define COIL_MODE_READER()         COIL_MODE= LOW
#define COIL_MODE_EMULATOR()       COIL_MODE= HIGH

// coil for emulation
#define COIL_OUT                   LATGbits.LATG9
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#define COIL_OUT_LOW()             COIL_OUT=LOW

// door relay (active low)
#define DOOR_RELAY                  LATAbits.LATA14
#define DOOR_RELAY_OPEN()           DOOR_RELAY= HIGH
#define DOOR_RELAY_CLOSE()          DOOR_RELAY= LOW

// inductance/capacitance freq
#define IC_FREQUENCY               PORTAbits.RA2

#define SNIFFER_COIL               PORTDbits.RD12    // external reader clock detect
#define READER_ANALOGUE            PORTBbits.RB11   // reader coil analogue
#define DIV_LOW_ANALOGUE           PORTBbits.RB12   // voltage divider LOW analogue
#define DIV_HIGH_ANALOGUE          PORTBbits.RB13   // voltage divider HIGH analogue

// clock coil (normally controlled by OC Module, but defined here so we can force it high or low)
#define CLOCK_COIL                 PORTDbits.RD4
#define CLOCK_COIL_MOVED           PORTDbits.RD0 // temporary for greenwire

// digital output after analogue reader circuit
#define READER_DATA                PORTDbits.RD8

// trace / debug
#define DEBUG_PIN_1                 LATCbits.LATC1
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#define LCR_CALIBRATE               LATBbits.LATB5

// wiegand / clock & data
#define WIEGAND_IN_0                PORTDbits.RD5
#define WIEGAND_IN_0_PULLUP         CNPUEbits.CNPUE14
#define WIEGAND_IN_0_PULLDOWN       CNPDbits.CNPD14
#define WIEGAND_IN_1                PORTDbits.RD6
#define WIEGAND_IN_1_PULLUP         CNPUEbits.CNPUE15
#define WIEGAND_IN_1_PULLDOWN       CNPDbits.CNPD15
#define CAND_IN_DATA                WIEGAND_IN_0
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#define CAND_OUT_CLOCK              WIEGAND_OUT_1

// connect/disconnect reader clock from coil - used to send RWD signals by creating gaps in carrier
#define READER_CLOCK_ENABLE         LATEbits.LATE9
#define READER_CLOCK_ENABLE_ON()    READER_CLOCK_ENABLE=CLOCK_ON
#define READER_CLOCK_ENABLE_OFF(x)  {READER_CLOCK_ENABLE=CLOCK_OFF; COIL_OUT=x;}

// these input pins must NEVER bet set to output or they will cause short circuits!
// they can be used to see data from reader before it goes into or gate
#define OR_IN_A                     PORTAbits.RA4
#define OR_IN_B                     PORTAbits.RA5


// CNCON and CNEN are set to allow wiegand input pin weak pullups to be switched on
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// Define the SPI frequency
#define SPI_FREQUENCY			(20000000)
// Description: SD-SPI Card Detect Input bit
#define SD_CD               PORTFbits.RF0
// Description: SD-SPI Card Detect TRIS bit
#define SD_CD_TRIS          TRISFbits.TRISF0
// Description: SD-SPI Write Protect Check Input bit
#define SD_WE               PORTFbits.RF1
// Description: SD-SPI Write Protect Check TRIS bit
#define SD_WE_TRIS          TRISFbits.TRISF1
// Description: The main SPI control register
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

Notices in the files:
firmware/Pic32/RFIDler.X/include/HardwareProfile.h:
A copy of the GNU GPL is appended to this file.
RFIDler is (C) 2013-2014 Aperture Labs Ltd.
under the terms of the GNU General Public License as published by the
Free Software Foundation; Version 2 ("GPL"), BUT ONLY WITH ALL OF THE
CLARIFICATIONS AND EXCEPTIONS DESCRIBED HEREIN.  This guarantees your
Note that the GPL places important restrictions on "derivative works",
yet it does not provide a detailed definition of that term.  To avoid
the plain GPL differently, so we consider this a special exception to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
